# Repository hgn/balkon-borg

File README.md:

# Balkon-Borg

## Assimilating vision, audio, and the radio spectrum - balcony intelligence

*Note: 'Balkon' is German for balcony. Alternatively, call it the ÜberBorg, as it hangs
"über" (over/above) you.*

A smart, local sensor-and-effector node for the balcony, tied into the home network.

**Sensors**

- Vision: camera (Raspberry Pi Camera Module 3; Frigate for person, animal and gesture recognition)
- Motion: radar (LD2410B; presence and motion detection)
- Acoustics: USB microphone (BirdNET, noise-level monitoring, audio event classification)
- Environment: sensor (BME280; temperature, humidity, pressure)
- Radio: SDR receiver (RTL-SDR V4; aircraft/ADS-B, FM/DAB+ and AM/shortwave broadcast (built-in HF front end), LoRa, 433/868 MHz weather and smart-home sensors, tire-pressure sensors/TPMS)
- Controls: physical interface (four illuminated buttons and a rotary encoder)

**Effectors**

- Light: LED panel (WLED RGBW via an Athom high-power controller; ambient to dynamic effects)
- Audio: speaker (Visaton BF 45 via a PAM8403 amp and a USB DAC; situational feedback and voice clips)
- Data: network stream (MQTT; telemetry to the borg-pi5 hub for dashboards and storage, reachable from outside through the always-on nas-Pi)

**Hardware core**

Raspberry Pi 5 ("borg-pi5") and a low-solder ESP32 front panel, off one shared 5 V feed.

---

## Preview

Enclosure (SLS/PA12, rounded edges, ceiling-mount ears, slogans embossed) and the
ESP32 sensor carrier board (fully placed and routed). **Click the enclosure image to
open the STL in GitHub's interactive 3D viewer** (`docs/img/enclosure.stl`, exported
by `make render`):

Four views of the current enclosure model as a clean line-art sheet, regenerated from
the CAD with `make -C cad views` (FreeCAD projects the STEP to hidden-line-removed 2D
views, matplotlib composes them):

The cable harness (which JST connector goes to which external part, with pinout and wire
colours) is board-specific detail and lives with the board: see
[`pcb/README.md`](pcb/README.md#wiring).

---

## Documentation

One bullet per document: short path, what it is for, and the link.

**What it does & why it is built this way**
- [`docs/use-cases.md`](docs/use-cases.md) — the binding list of what the unit does (U1–U20), each with its requirements, value and planned implementation.
- [`log/decisions.md`](log/decisions.md) — the hardware decision log: why every enclosure, PCB, power and wiring choice is the way it is, and which alternatives were rejected.
- [`src/log/decisions.md`](src/log/decisions.md) — the software decision log: architecture, protocol, data-contract and stack choices.

**Software stack**
- [`src/README.md`](src/README.md) — layout of the software stack (Pi, ESP32 app, Android, shared) and the still-open questions.
- [`src/architecture.md`](src/architecture.md) — the whole-system concept: the four resource axes, how features combine, the mode model and data flow.

**Hardware & build**
- [`docs/network.md`](docs/network.md) — how the borg-pi5, ESP32 and nas-Pi talk, plus the MQTT topic scheme.
- [`docs/wiring.md`](docs/wiring.md) — terminal assignment and the GPIO / I²C / Wago plan.
- [`docs/power-distribution.md`](docs/power-distribution.md) — the 5 V fused star and the external IP66 PSU box.
- [`docs/build-notes.md`](docs/build-notes.md) — hands-on integration notes (Pi power, flashing, antenna, camera, speaker).
- [`docs/enclosure-sintering.md`](docs/enclosure-sintering.md) — SLS/PA12 manufacturing rules and print providers.
- [`docs/light-scenarios.md`](docs/light-scenarios.md) — the catalogue of WLED light scenes (L1–L12).
- [`pcb/docs/board-spec.md`](pcb/docs/board-spec.md) — the binding carrier-board spec, the source of truth for the PCB.
- [`cad/README.md`](cad/README.md) — the parametric CadQuery enclosure: how to build and regenerate it.
- [`pcb/README.md`](pcb/README.md) — the carrier board: the netlist-from-code → place → route → fabricate flow.

**Review, cost, manual**
- [`docs/design-review.md`](docs/design-review.md) — the ranked whole-system review findings, severity-tagged.
- [`docs/cost-estimate.md`](docs/cost-estimate.md) — the bill of materials and running cost (ordered items are actuals).
- [`manual/manual-de.pdf`](manual/manual-de.pdf) · [`manual/manual-en.pdf`](manual/manual-en.pdf) — the illustrated step-by-step build manual (German / English).

---

## 1 · Short description

A compact enclosure, screwed under the balcony (above the terrace, ~2 m from the
dining table), bundling several functions: mood-to-party lighting, presence and
environment sensing, aircraft reception (ADS-B) and bird-call recognition. Everything
runs off a shared 5 V feed and an MQTT/WiFi bus. The goal is a build that looks
*intentional* (one box, one light field, minimal cabling) rather than tinkered.

## 2 · Goals

- **One visible box, minimal cabling**: exactly one 230 V feed, everything else 5 V + radio.
- **Value over gimmick**: automations and data actually used day to day (light at the table, weather, birds, aircraft).
- **Cleanly integrated into the existing setup**: MQTT bus, Podman/Quadlets, live-only (no telemetry database).
- **Maintainable and extensible**: low-solder, pre-flashed components; enclosure as parametric code (CadQuery), not a throwaway click model.
- **Reliable continuous outdoor operation** (protected), thermally and electrically designed for summer duty.

## 3 · Use cases

The unit's functions are specified as **21 use cases (U1–U21)** — table lighting,
manual and gesture control, effect light, environment data, aircraft and bird
reception, radio (FM/DAB+/shortwave), a scanner for ADS-B and ISM sensors, a security
suite, a live camera view with app talk-down, and more. Each with its requirements, value
and planned implementation lives in [`docs/use-cases.md`](docs/use-cases.md), the binding
list of what gets built.

## 4 · System components (current state)

- **Central compute (borg-pi5):** Raspberry Pi 5 (8 GB) + Active Cooler, microSD in the enclosure, **the hub the project is about**: recording (camera/audio/SDR), local inference (Frigate, readsb/tar1090, BirdNET-Go), and the **MQTT broker (Mosquitto), dashboards and app**. Powered on **only when needed**, not 24/7.
- **Sensor/control front panel:** ESP32 (ESPHome) with LD2410B (UART), BME280 (I²C), 4 buttons + encoder (GPIO).
- **Light:** Athom high-power WLED controller + SK6812 RGBW-WW light field: 8 rows of 60/m strip, 25 LEDs each = 200 px, on a 3 mm aluminium plate (438 × 88, bought cut to size), opal acrylic diffuser.
- **Reception:** RTL-SDR V4 (ADS-B 1090 MHz, FM/DAB+/shortwave listening, optional LoRa RX), USB microphone (on the Pi 5). The LD2410B radar points **forward** (in the LED tower), toward the terrace.
- **Audio out:** USB sound card (C-Media, e.g. DELOCK 61645) + a **PAM8403** mini class-D amp + a **Visaton BF 45** broadband speaker on the borg-pi5, plays a short wav on events (detection, greeting). The Pi 5 has no analogue output, hence the USB card; amp powered off the Pi's 5 V branch (see [power](docs/power-distribution.md)).
- **Power:** Mean Well LRS-150F-5 (5 V/22 A) in its own external **IP66 ceiling box**, fused 5 V branches into the enclosure (see [power distribution](docs/power-distribution.md)).
- **Enclosure:** 3D print in SLS/PA12 (black), **two halves** split at X=0 (each ~254 mm, fits a standard SLS bed such as JLC3DP), bolted with internal M3 seam clamps and 4 mm dowel pins; a 3 mm aluminium plate behind the diffuser carries the LED strips.
- **nas-Pi5 (existing, minor role):** a separate, **always-on** Raspberry Pi 5 wired to the Fritz!Box. Only the **remote-access point** (reach the unit from outside) and occasional **image/data storage**, not the hub (see [network](docs/network.md)).

## 5 · Architecture and data flow

The **borg-pi5** is the hub: it captures camera (CSI), audio (USB) and RF (USB SDR), runs
the object recognition locally, and hosts the **MQTT broker, dashboards and app**, only
events and metadata go on over MQTT, no continuous raw stream. The **ESP32** handles the
human-facing, real-time-critical I/O (buttons, encoder, radar) and the slow environment
sensors; it is deliberately the *cheap, replaceable front panel*. The **nas-Pi5** is only
a minor, always-on helper (remote access + occasional image storage); the borg-pi5 runs
when needed, so its light/MQTT automation is available while it is on. Path: borg-pi5 →
WiFi repeater → cable → Fritz!Box → nas-Pi5 (see [network](docs/network.md)).

## 6 · Constraints

**Environment**
- Mounting location on the balcony underside: **rain-protected**, but raised humidity possible; Munich **summer heat** is relevant.
- No true IP65 needed (protected location) → **ventilated** enclosure with slits facing down + insect protection.

**Electrical**
- Exactly **one 230 V feed** (terrace socket, RCD-protected); target picture "no thousand cables".
- One shared **5 V PSU**, fused branches (10 A LED / 5 A Pi / 2 A small electronics), common GND, trimmer to **5.15 V**.
- **Fire safety:** the 230 V PSU **separated** from the printed part (its own V-0/metal enclosure); the printed part carries low voltage only.

**Thermal**
- **Aluminium plate = heatsink** of the LED layer, thermal contact to the enclosure (thermal pad at the supports).
- Pi 5 continuous load (now incl. **CPU object recognition**) → Active Cooler + ventilation are critical, not optional.
- WLED **Automatic Brightness Limiter** at ~8 A → caps the panel's heat and current.

**Mechanical / manufacturing**
- **3D print in SLS/PA12**, black-dyed (no supports, no layer lines, production look). See `docs/enclosure-sintering.md`.
- Printed as **two halves** (each ~254 mm, fits a standard SLS bed) and bolted together with M3 seam clamps and 4 mm dowel pins; black PA12 (e.g. JLC3DP 3201PA-F). Splitting keeps it off the expensive large-bed services.
- Radar sits in the LED tower (forward view); the **camera looks forward** to the terrace from a downward-hanging box (open at the top, set back, tilted ~24° down so the housing stays out of frame), not straight down.

**Network**
- WiFi + MQTT as the bus; **Ethernet optional** (only makes the video stream more bulletproof).

**Skill level / preferences**
- Soldering and programming available, **not a full tinkerer** → solder-free/pre-flashed parts preferred (Athom pre-flashed, pluggable LED connectors, buttons with a pigtail).
- **Quality over price**: reflected in RGBW-WW (real warm white), stainless buttons, SLS.

**Budget**
- **~415 €** new parts + **~40 €** odds and ends (connectors, fuses, Wago, wire, screws, inserts, glands). Camera and NAS-Pi already on hand.

## 7 · Key risks

- **Thermal in summer**: CPU detection raises the continuous load; ventilation and the Active Cooler decide stability.
- **Recognition performance**: without an NPU, FPS/stream limited; possibly a lighter model or a later Hailo retrofit.
- **Humidity/condensation**: mind the downward ventilation and possibly pressure equalisation so nothing collects.

## 8 · Built with Claude (Fable 5)

The complete hardware design in this repo, the parametric CadQuery enclosure, the
SKiDL → KiCad → Freerouting carrier board, the ESPHome firmware, the MQTT/Podman
plumbing and the docs, was generated in collaboration with Anthropic's **Claude**
**Fable 5**, driving the CAD, PCB, render and review tooling directly.
For the curious, a `/context` snapshot from one of the working sessions:

```text
Context Usage
⛁ ⛁ ⛁ ⛁ ⛀ ⛁ ⛁ ⛁ ⛁ ⛁ ⛁ ⛁ ⛁ ⛁ ⛁ ⛁ ⛁ ⛁ ⛁ ⛁   Fable 5
⛁ ⛁ ⛁ ⛁ ⛁ ⛁ ⛁ ⛁ ⛁ ⛁ ⛁ ⛁ ⛁ ⛁ ⛁ ⛁ ⛁ ⛁ ⛁ ⛁   claude-fable-5
⛁ ⛁ ⛁ ⛁ ⛁ ⛁ ⛁ ⛁ ⛁ ⛁ ⛁ ⛁ ⛁ ⛁ ⛁ ⛁ ⛁ ⛁ ⛁ ⛁   323k/1m tokens (32%)
⛁ ⛁ ⛁ ⛁ ⛁ ⛀ ⛶ ⛶ ⛶ ⛶ ⛶ ⛶ ⛶ ⛶ ⛶ ⛶ ⛶ ⛶ ⛶ ⛶
⛶ ⛶ ⛶ ⛶ ⛶ ⛶ ⛶ ⛶ ⛶ ⛶ ⛶ ⛶ ⛶ ⛶ ⛶ ⛶ ⛶ ⛶ ⛶ ⛶   Estimated usage by category
⛶ ⛶ ⛶ ⛶ ⛶ ⛶ ⛶ ⛶ ⛶ ⛶ ⛶ ⛶ ⛶ ⛶ ⛶ ⛶ ⛶ ⛶ ⛶ ⛶   ⛁ System prompt:  3.9k tokens (0.4%)
⛶ ⛶ ⛶ ⛶ ⛶ ⛶ ⛶ ⛶ ⛶ ⛶ ⛶ ⛶ ⛶ ⛶ ⛶ ⛶ ⛶ ⛶ ⛶ ⛶   ⛁ System tools:   8.8k tokens (0.9%)
⛶ ⛶ ⛶ ⛶ ⛶ ⛶ ⛶ ⛶ ⛶ ⛶ ⛶ ⛶ ⛶ ⛶ ⛶ ⛶ ⛶ ⛶ ⛶ ⛶   ⛁ Memory files:   5.6k tokens (0.6%)
⛶ ⛶ ⛶ ⛶ ⛶ ⛶ ⛶ ⛶ ⛶ ⛶ ⛶ ⛶ ⛶ ⛶ ⛶ ⛶ ⛶ ⛶ ⛶ ⛶   ⛁ Skills:         2.6k tokens (0.3%)
⛶ ⛶ ⛶ ⛶ ⛶ ⛶ ⛶ ⛶ ⛶ ⛶ ⛶ ⛶ ⛶ ⛶ ⛶ ⛶ ⛶ ⛶ ⛶ ⛶   ⛁ Messages:     302.8k tokens (30.3%)
                                        ⛶ Free space:   676.4k (67.6%)

MCP tools · 25 tools · loaded on-demand
Memory files · 3 files · 5.6k tokens
Skills · 21 skills · 2.6k tokens
```

The bulk (the "Messages" slice) is the working transcript: CAD builds and OpenCascade
booleans, KiCad/pcbnew scripting, Freerouting runs, DRC reports and render round-trips.

### Who did what

The honest split: **the author has no background in hardware design, electronics,
schematics or PCB layout**, this project would simply not exist without Claude. The
human side was defining the **use cases and requirements** and stepping in only where
it was unavoidable (a few KiCad steps). The actual engineering, the parametric
enclosure, the schematic and board, the routing, the firmware, the DfAM and signal-flow
reviews, was done by **Claude (Fable 5)**.

### Token usage and cost

Measured with [`ccusage`](https://github.com/ryoppippi/ccusage) over three working days
(10–12 Jul 2026, Fable 5, ccusage tags the sessions `opus-4-8`, an app-side model-label
quirk; the work ran on Fable 5):

| Day | Input | Output | Cache write | Cache read | Total tokens | Cost |
|---|--:|--:|--:|--:|--:|--:|
| 2026-07-10 | 9,200 | 625,879 | 2,536,382 | 103,796,715 | 106,968,176 | $92.96 |
| 2026-07-11 | 28,183 | 671,930 | 2,860,378 | 203,925,544 | 207,486,035 | $147.51 |
| 2026-07-12 | 21,093 | 560,556 | 5,245,511 | 188,015,314 | 193,842,474 | $160.58 |
| 2026-07-13 | 13,406 | 428,986 | 3,808,720 | 115,205,441 | 119,456,553 | $106.48 |
| **Total** | **71,882** | **2,287,351** | **14,450,991** | **610,943,014** | **≈628 M** | **$507.53** |

So a complete, fabrication-ready hardware package, SLS enclosure, routed carrier board,
firmware, a build manual and docs, for **about $508** (≈470 €) of model usage over four
days. Over 600 million tokens, most of it cache reads (re-reading the growing repo and
transcript each turn), which is why the token count is huge but the cost is not.

For scale: a freelance hardware developer taking on the same scope (enclosure CAD,
schematic + board layout + routing, firmware, and the write-up) would realistically
spend a few weeks, in the low-to-mid **five figures in euros**. The point is not that
Claude is "cheaper by X"; it is that a person with zero hardware background got to a
buildable design at all.

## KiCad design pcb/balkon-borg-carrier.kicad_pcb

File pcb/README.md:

# pcb — Sensor carrier board (KiCad)

The ESP32 front panel: THT, 2 layers, made at Aisler. Binding source of truth:
[`docs/board-spec.md`](docs/board-spec.md). Decisions are in the project log
(`../log/decisions.md`).

## Flow (netlist from code, layout scripted)

The schematic — including the correct ESP32-DevKitC-V4 pin mapping — is described in
code and turned into a KiCad netlist; placement and routing are scripted so the
board is reproducible.

1. **Netlist** from `gen-netlist.py` (SKiDL) → `balkon-borg-carrier.net`:
   ```
   make -C pcb netlist
   ```
2. **Import** the netlist into a fresh `balkon-borg-carrier.kicad_pcb` with
   `kinet2pcb` (footprints + nets), or start from the committed board.
3. **Place + route** (one-time, headless): `place-board.py` lays out the footprints,
   draws the outline, adds the mounting holes and the "HagiOne" silkscreen, sets the
   Aisler DRC minimums, exports a Specctra DSN; Freerouting autoroutes it;
   `apply-ses.py` imports the session back. (Freerouting is an external tool, not
   vendored.)
4. **Ground pour**:
   ```
   make -C pcb pour           # GND pour (both layers) + antenna keep-out
   ```
5. **Verify** before ordering (headless, no GUI, no manual steps):
   ```
   make -C pcb verify         # ERC, DRC, netlist<->board, spec, fab outputs
   ```
   See [Verification](#verification) below.
6. **Fabrication outputs**:
   ```
   make -C pcb outputs        # gerbers/drill/pos + Aisler zip into output/
   ```
   The committed board is fully routed and DRC-clean (0 violations, 0 unconnected).
7. Upload the gerber zip to **Aisler**.

## Verification

`make -C pcb verify` runs the whole check unattended and exits non-zero if
anything is off, so it is safe to trust before spending money on a fab run. Five
stages:

1. **SKiDL ERC** — regenerates the netlist and runs the electrical rule check
   (unconnected ESP header pins are expected warnings, not errors).
2. **KiCad DRC** — `kicad-cli` geometry, clearance, track width and silk checks.
3. **netlist ↔ board** — the committed board has not drifted from the code. The
   compare is by connectivity, not net name, so it survives SKiDL's auto-naming.
4. **board-spec intent** — connector pinouts and series-resistor values match
   [`docs/board-spec.md`](docs/board-spec.md). This is the one check a DRC cannot
   do: it catches a swapped connector pin or a wrong resistor value. The
   GPIO-number-to-header-pin mapping is out of scope (it needs the external
   DevKitC-V4 pinout as ground truth).
5. **fab outputs** — exports the gerber and drill set, confirms it is a two-layer
   stack (F.Cu, B.Cu, Edge.Cuts), and renders a top PNG when a GL backend exists.

## Files

- `gen-netlist.py` — SKiDL script, builds the netlist from `docs/board-spec.md`.
- `place-board.py` / `apply-ses.py` — headless placement and Specctra-session import
  (run with the system python, which has the KiCad `pcbnew` module).
- `add-ground-pour.py` — GND pour + antenna keep-out, run in three phases (`make pour`);
  the phases must be separate processes (pcbnew drops the rule area otherwise).
- `scripts/gen-outputs.py` — fabrication output via `kicad-cli`.
- `verify.py` — orchestrates the five verification stages (`make verify`).
- `check-netlist-board.py` / `check-board-spec.py` — the netlist↔board and
  board-spec intent checks; `netparse.py` is the shared netlist parser.

## Conventions

Comments/net names in English. THT only, JST-XH 2.5 mm, generous spacing. Change the
schematic only in `gen-netlist.py`, then regenerate the netlist and re-import.

## Wiring

The cable harness from the carrier board's JST connectors to the external components,
shown two ways. Both are **generated from the netlist** (`make -C pcb harness`), so they
cannot silently disagree with the board.

Schematic harness (pinout + wire colours), rendered by **WireViz** from
[`wiring-harness.yaml`](wiring-harness.yaml) — click for the zoomable SVG:

The same connections on the board render, with callouts placed by
[`annotate-board.py`](annotate-board.py) from the connector positions
([full-resolution PNG](docs/img/board-annotated.png)):

Terminal assignment and the GPIO/I²C/Wago plan behind these images live in
[`../docs/wiring.md`](../docs/wiring.md).

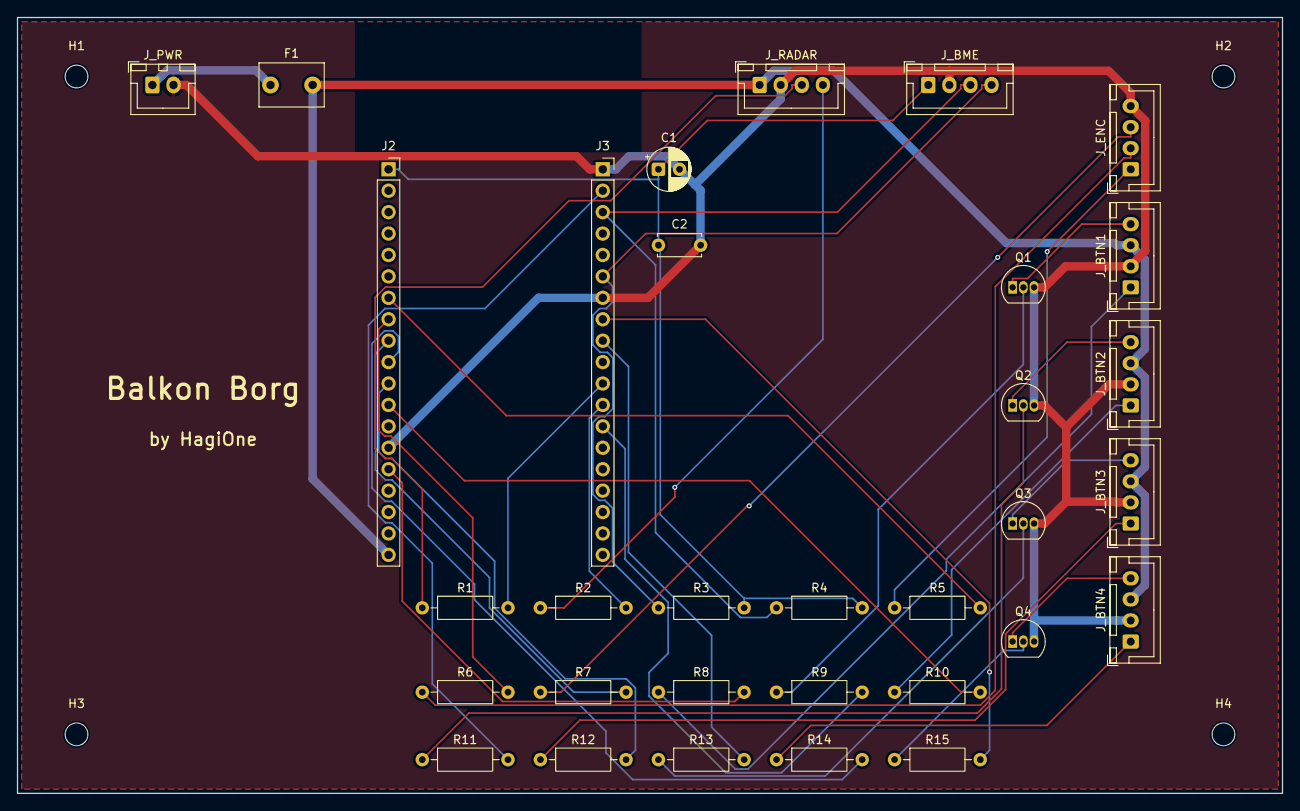
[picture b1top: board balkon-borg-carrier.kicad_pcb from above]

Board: 2 copper layers, 150.0 x 92.0 mm, 36 parts (0 on the bottom side), 36 nets.

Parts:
C1: 10uF; CP_Radial_D5.0mm_P2.50mm
C2: 100nF; C_Disc_D5.0mm_W2.5mm_P5.00mm
F1: 2A; C_Disc_D7.5mm_W5.0mm_P5.00mm
H1, H2, H3, H4: MountingHole_2.7mm_M2.5
J2: ESP32-DevKitC L; PinSocket_1x19_P2.54mm_Vertical
J3: ESP32-DevKitC R; PinSocket_1x19_P2.54mm_Vertical
J_BME: BME280; JST_XH_B4B-XH-A_1x04_P2.50mm_Vertical
J_BTN1, J_BTN2, J_BTN3, J_BTN4: Taster; JST_XH_B4B-XH-A_1x04_P2.50mm_Vertical
J_ENC: Encoder EC11; JST_XH_B4B-XH-A_1x04_P2.50mm_Vertical
J_PWR: 5V in; JST_XH_B2B-XH-A_1x02_P2.50mm_Vertical
J_RADAR: LD2410B; JST_XH_B4B-XH-A_1x04_P2.50mm_Vertical
Q1, Q2, Q3, Q4: BC337; TO-92_Inline
R1, R2: 220; R_Axial_DIN0207_L6.3mm_D2.5mm_P10.16mm_Horizontal
R3, R4: 4k7; R_Axial_DIN0207_L6.3mm_D2.5mm_P10.16mm_Horizontal
R5, R6, R7, R8, R10, R12, R14: 100; R_Axial_DIN0207_L6.3mm_D2.5mm_P10.16mm_Horizontal
R9, R11, R13, R15: 1k; R_Axial_DIN0207_L6.3mm_D2.5mm_P10.16mm_Horizontal

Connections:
+3V3: C1.1, C2.1, J2.1, J_BME.1, R3.2, R4.2
+5V: F1.2, J2.19, J_BTN1.3, J_BTN2.3, J_BTN3.3, J_BTN4.3, J_RADAR.1
+5V_IN: F1.1, J_PWR.1
BTN1_LEDK: J_BTN1.4, Q1.1
BTN1_SW: J_BTN1.1, R8.1
BTN2_LEDK: J_BTN2.4, Q2.1
BTN2_SW: J_BTN2.1, R10.1
BTN3_LEDK: J_BTN3.4, Q3.1
BTN3_SW: J_BTN3.1, R12.1
BTN4_LEDK: J_BTN4.4, Q4.1
BTN4_SW: J_BTN4.1, R14.1
ENC_A: J_ENC.1, R5.1
ENC_B: J_ENC.2, R6.1
ENC_SW: J_ENC.3, R7.1
GND: C1.2, C2.2, J2.14, J3.1, J3.7, J_BME.2, J_BTN1.2, J_BTN2.2, J_BTN3.2, J_BTN4.2, J_ENC.4, J_PWR.2, J_RADAR.2, Q1.3, Q2.3, Q3.3, Q4.3
I2C_SCL: J3.3, J_BME.3, R4.1
I2C_SDA: J3.6, J_BME.4, R3.1
unnamed: J3.11, R1.2
unnamed: J3.12, R2.2
unnamed: J2.7, R5.2
unnamed: J2.8, R6.2
unnamed: J2.9, R7.2
unnamed: J2.15, R8.2
unnamed: Q1.2, R9.1
unnamed: J3.13, R9.2
unnamed: J2.12, R10.2
unnamed: Q2.2, R11.1
unnamed: J3.2, R11.2
unnamed: J2.11, R12.2
unnamed: Q3.2, R13.1
unnamed: J3.9, R13.2
unnamed: J2.10, R14.2
unnamed: Q4.2, R15.1
unnamed: J3.8, R15.2
RADAR_RX: J_RADAR.3, R1.1
RADAR_TX: J_RADAR.4, R2.1

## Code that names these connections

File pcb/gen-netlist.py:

#!/usr/bin/env python3
"""Generate the KiCad netlist for the Balkon-Borg sensor carrier via SKiDL.

The board (see docs/board-spec.md) is the ESP32 front plate: an ESP32-DevKitC-V4
socketed on two 1x19 headers, JST-XH connectors for radar, BME280, encoder and
four illuminated buttons, series resistors, NPN LED drivers and decoupling.

ESP pin positions follow the official ESP32-DevKitC-V4 header layout (J2 left,
J3 right, top to bottom). Run this, then import the .net into the KiCad PCB
editor and lay the board out.

    KICAD9_SYMBOL_DIR / KICAD9_FOOTPRINT_DIR must point at the KiCad libraries.
    python gen-netlist.py   ->   balkon-borg-carrier.net
"""

import argparse
import os
import sys
from pathlib import Path

os.environ.setdefault("KICAD9_SYMBOL_DIR", "/usr/share/kicad/symbols")
os.environ.setdefault("KICAD9_FOOTPRINT_DIR", "/usr/share/kicad/footprints")

from skidl import ERC, KICAD9, Net, Part, generate_netlist, set_default_tool  # noqa: E402
from skidl.logger import erc_logger  # noqa: E402

set_default_tool(KICAD9)

FP_HDR = "Connector_PinSocket_2.54mm:PinSocket_1x19_P2.54mm_Vertical"
FP_J2 = "Connector_JST:JST_XH_B2B-XH-A_1x02_P2.50mm_Vertical"
FP_J4 = "Connector_JST:JST_XH_B4B-XH-A_1x04_P2.50mm_Vertical"
FP_J5 = "Connector_JST:JST_XH_B5B-XH-A_1x05_P2.50mm_Vertical"
FP_R = "Resistor_THT:R_Axial_DIN0207_L6.3mm_D2.5mm_P10.16mm_Horizontal"
FP_CD = "Capacitor_THT:C_Disc_D5.0mm_W2.5mm_P5.00mm"
FP_CP = "Capacitor_THT:CP_Radial_D5.0mm_P2.50mm"
FP_Q = "Package_TO_SOT_THT:TO-92_Inline"
FP_PTC = "Capacitor_THT:C_Disc_D7.5mm_W5.0mm_P5.00mm"  # radial 2-lead PTC (5 mm pitch);
# VERIFY against the actual polyfuse part — a PTC is radial, not an axial resistor.


def res(val: str) -> Part:
    return Part("Device", "R", value=val, footprint=FP_R)


def conn(name: str, npins: int, fp: str, value: str) -> Part:
    return Part("Connector_Generic", f"Conn_01x{npins:02d}", ref=name,
                footprint=fp, value=value)


p5v, p3v3, gnd = Net("+5V"), Net("+3V3"), Net("GND")

# ESP32-DevKitC-V4, socketed on two 1x19 headers (J2 = left, J3 = right).
espL = Part("Connector_Generic", "Conn_01x19", ref="J2",
            footprint=FP_HDR, value="ESP32-DevKitC L")
espR = Part("Connector_Generic", "Conn_01x19", ref="J3",
            footprint=FP_HDR, value="ESP32-DevKitC R")
p5v += espL[19]          # J2.19 = 5V input to the DevKit
p3v3 += espL[1]          # J2.1  = 3V3 output from the DevKit regulator
gnd += espL[14], espR[1], espR[7]

# GPIO -> physical header pin (per DevKitC-V4 layout)
GPIO34, GPIO32, GPIO33, GPIO25 = espL[5], espL[7], espL[8], espL[9]
GPIO26, GPIO27, GPIO14, GPIO13 = espL[10], espL[11], espL[12], espL[15]
GPIO23, GPIO22, GPIO21 = espR[2], espR[3], espR[6]
GPIO19, GPIO18, GPIO17, GPIO16, GPIO4 = espR[8], espR[9], espR[11], espR[12], espR[13]


def series(outside, esp_pin, val: str, netname: str) -> None:
    """Outside connector pin -> series resistor -> ESP GPIO, named net outside."""
    r = res(val)
    Net(netname).connect(outside, r[1])
    r[2] += esp_pin


# 5 V input with resettable fuse.
jpwr = conn("J_PWR", 2, FP_J2, "5V in")
f1 = Part("Device", "Polyfuse", ref="F1", value="2A", footprint=FP_PTC)
Net("+5V_IN").connect(jpwr[1], f1[1])
f1[2] += p5v
gnd += jpwr[2]

# 3V3 decoupling.
c1 = Part("Device", "C", ref="C1", value="10uF", footprint=FP_CP)
c2 = Part("Device", "C", ref="C2", value="100nF", footprint=FP_CD)
for c in (c1, c2):
    p3v3 += c[1]
    gnd += c[2]

# Radar LD2410B (5V, GND, RX, TX) with 220R series. Presence comes over UART, so the
# separate OUT pin (GPIO34) is dropped (M10: it was dead copper) -> 4-pin connector.
jrad = conn("J_RADAR", 4, FP_J4, "LD2410B")
p5v += jrad[1]
gnd += jrad[2]
series(jrad[3], GPIO17, "220", "RADAR_RX")   # ESP TX2 -> radar RX
series(jrad[4], GPIO16, "220", "RADAR_TX")   # radar TX -> ESP RX2

# BME280 (3V3, GND, SCL, SDA), direct I2C + optional 4k7 pull-ups (DNP-capable).
jbme = conn("J_BME", 4, FP_J4, "BME280")
p3v3 += jbme[1]
gnd += jbme[2]
sda, scl = Net("I2C_SDA"), Net("I2C_SCL")
sda += jbme[4], GPIO21
scl += jbme[3], GPIO22
rsda, rscl = res("4k7"), res("4k7")
sda += rsda[1]
scl += rscl[1]
p3v3 += rsda[2], rscl[2]

# Rotary encoder EC11 (A, B, SW, GND) with 100R series.
jenc = conn("J_ENC", 4, FP_J4, "Encoder EC11")
series(jenc[1], GPIO32, "100", "ENC_A")
series(jenc[2], GPIO33, "100", "ENC_B")
series(jenc[3], GPIO25, "100", "ENC_SW")
gnd += jenc[4]

# Four illuminated buttons: SW via 100R; 5V LED switched low-side by an NPN.
btn_sw = [GPIO13, GPIO14, GPIO27, GPIO26]
btn_led = [GPIO4, GPIO23, GPIO18, GPIO19]
for i in range(4):
    jb = conn(f"J_BTN{i + 1}", 4, FP_J4, "Taster")
    series(jb[1], btn_sw[i], "100", f"BTN{i + 1}_SW")     # switch to GPIO
    gnd += jb[2]                                          # switch return
    p5v += jb[3]                                          # LED anode
    q = Part("Transistor_BJT", "BC337", ref=f"Q{i + 1}",
             footprint=FP_Q, value="BC337")
    Net(f"BTN{i + 1}_LEDK").connect(jb[4], q["C"])        # LED cathode -> collector
    rb = res("1k")
    q["B"] += rb[1]
    rb[2] += btn_led[i]                                  # base driven from GPIO
    gnd += q["E"]

if __name__ == "__main__":
    ap = argparse.ArgumentParser(description="Generate the carrier netlist.")
    ap.add_argument("--strict", action="store_true",
                    help="run ERC and exit non-zero if it reports any error")
    args = ap.parse_args()

    ERC()
    errors = erc_logger.error.count + erc_logger.bare_error.count
    warnings = erc_logger.warning.count + erc_logger.bare_warning.count
    print(f"ERC: {errors} error(s), {warnings} warning(s) "
          "(unconnected ESP header pins are expected warnings)", file=sys.stderr)

    out = Path(__file__).parent / "balkon-borg-carrier.net"
    generate_netlist(file_=str(out))
    print(f"wrote {out}")

    if args.strict and errors:
        print(f"ERC failed with {errors} error(s)", file=sys.stderr)
        raise SystemExit(1)
